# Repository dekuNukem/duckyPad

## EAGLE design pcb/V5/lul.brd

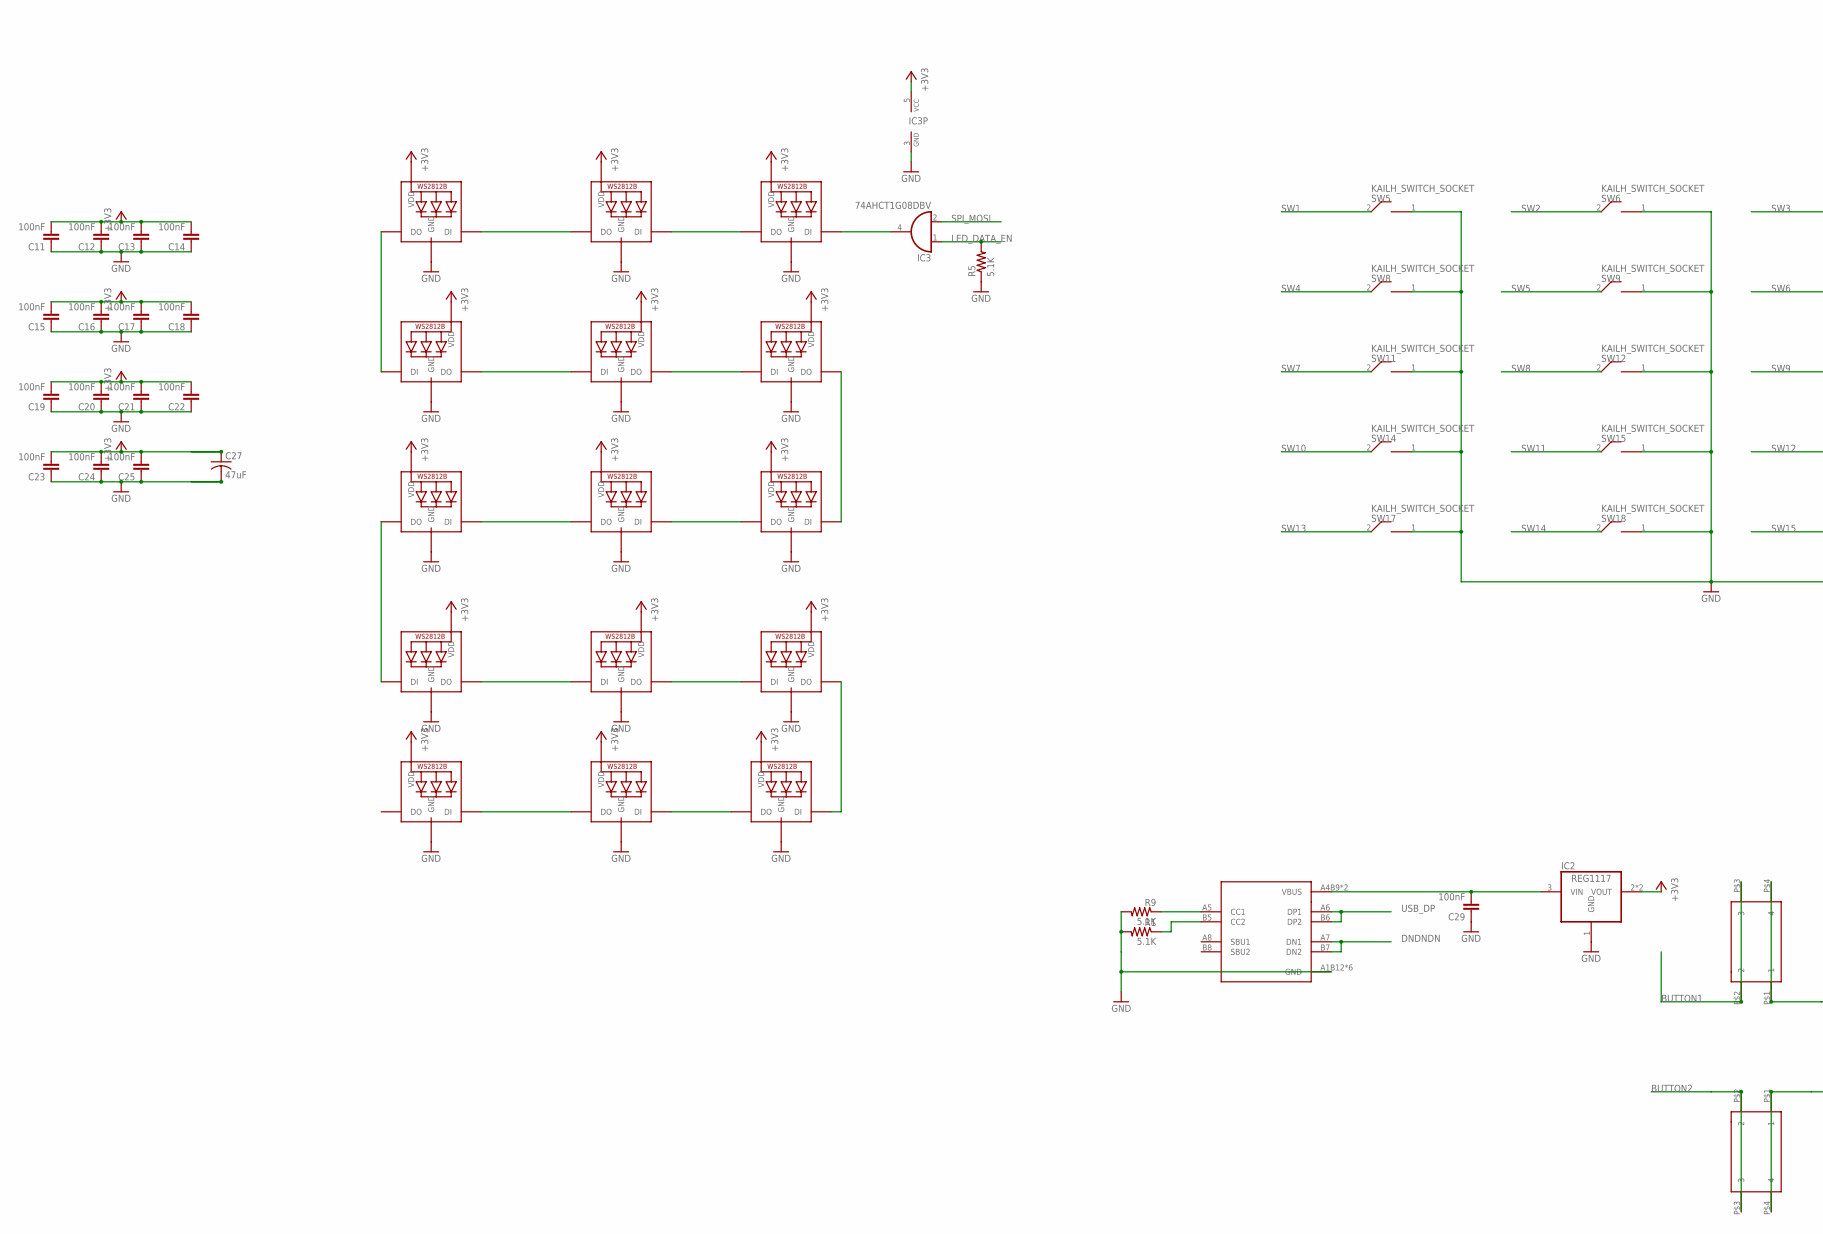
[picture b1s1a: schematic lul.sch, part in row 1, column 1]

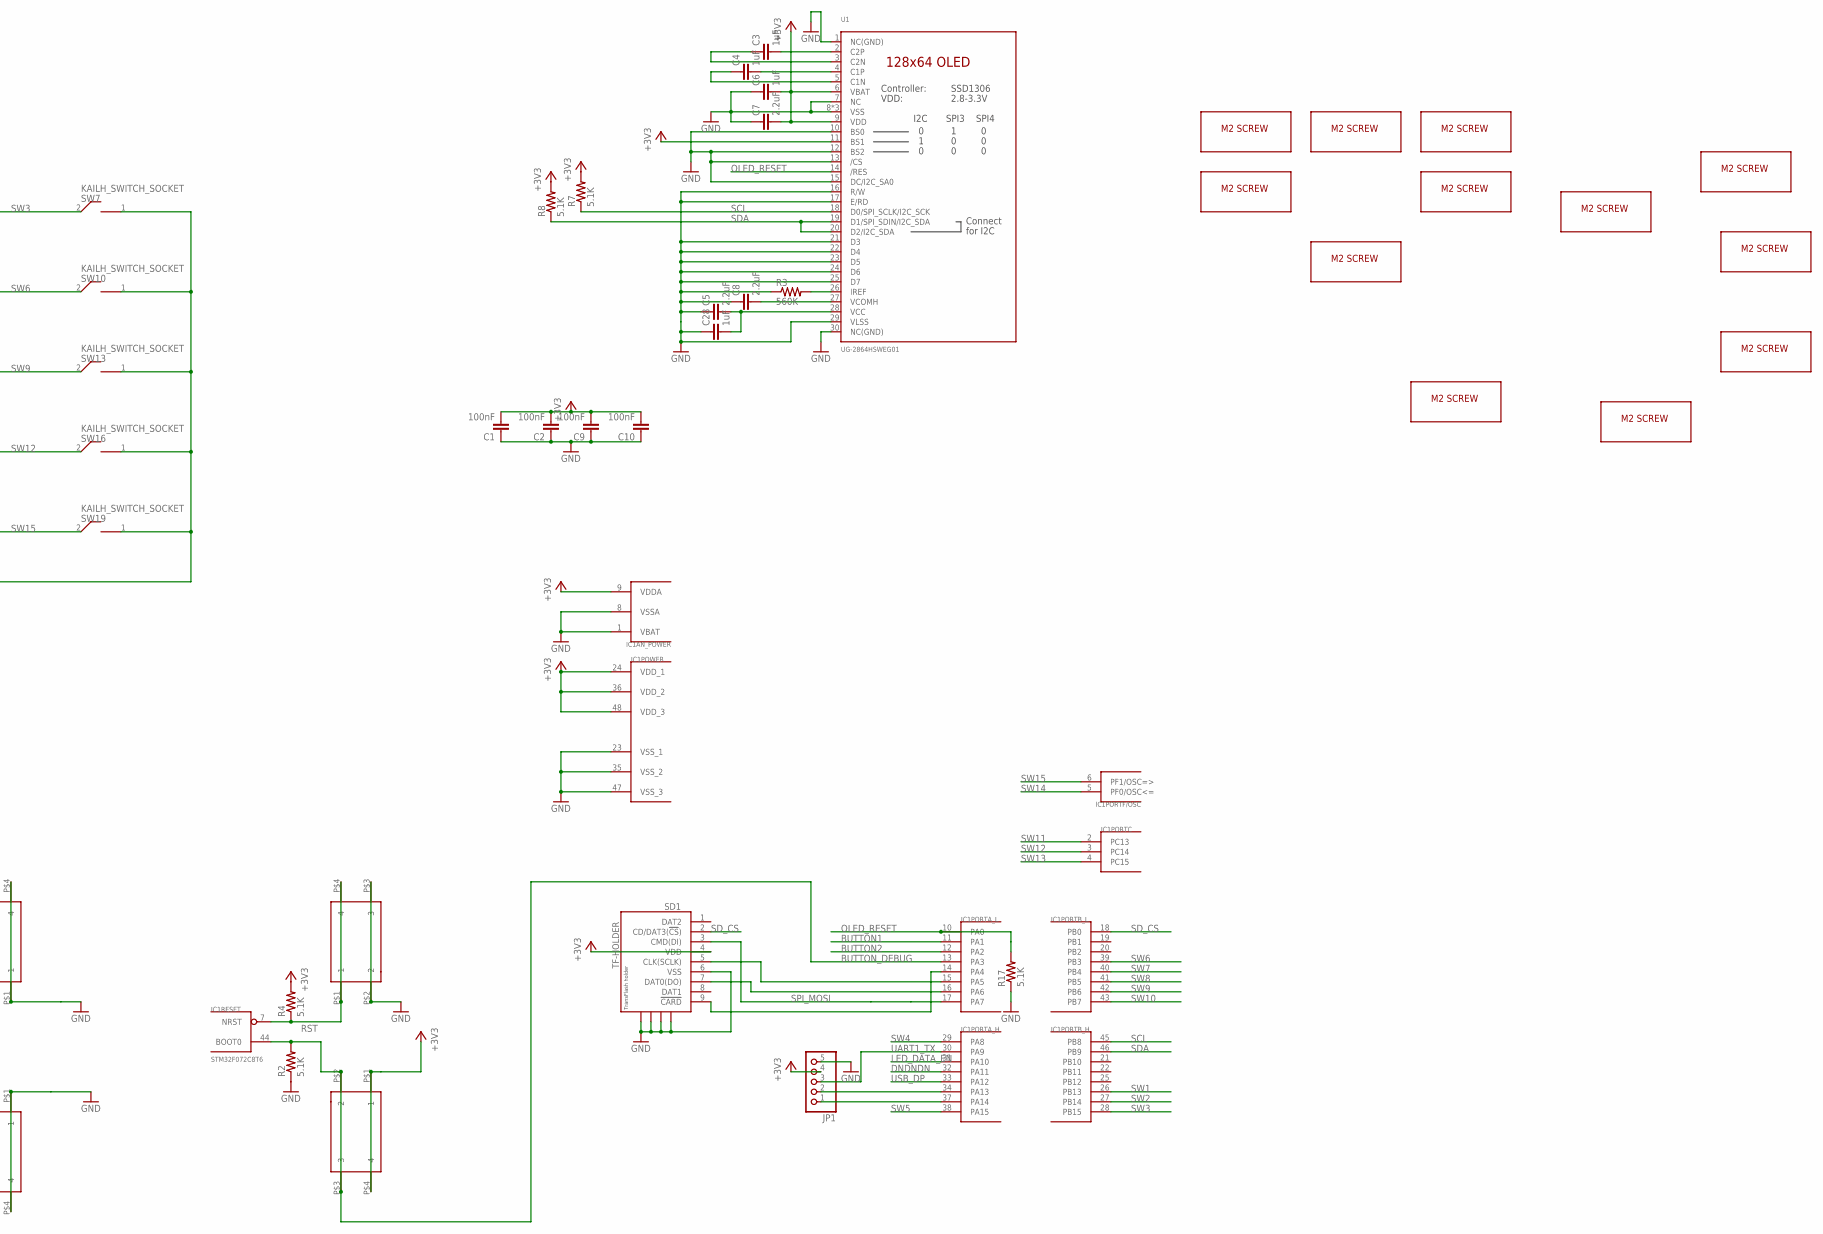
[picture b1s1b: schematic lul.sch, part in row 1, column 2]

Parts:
C1, C2, C9, C10, C11, C12, C13, C14, C15, C16, C17, C18, C19, C20, C21, C22, C23, C24, C25, C29: 100nF; 0805@1
C3, C4, C6, C28: 1uF; 0805@1
C5, C7, C8: 2.2uF; 0805@1
C27: 47uF; C1210
IC1: STM32F072C8T6; TQFP48
IC2: REG1117; SOT223
IC3: 74AHCT1G08DBV; SOT23-5
JP1: PINHD-1X5; 1X05
LED1, LED2, LED3, LED4, LED5, LED6, LED7, LED8, LED9, LED10, LED11, LED12, LED13, LED14, LED15: WS2812B; REVERSE_MNT
R1, R2, R4, R5, R7, R8, R9, R17: 5.1K; 0805
R3: 560K; 0805
SD1: TF-HOLDER; TF-PULL
SW1, SW2: 324_SW324_SWITCH_FOOT_HOLE; 342_SWICH_FOOT_HOLE
SW3, SW4: 324_SW; 342_SWICH_FOOT
SW5, SW6, SW7, SW8, SW9, SW10, SW11, SW12, SW13, SW14, SW15, SW16, SW17, SW18, SW19: KAILH_SWITCH_SOCKET; SWITCH_SOCKET
U1: UG-2864HSWEG01; LUL_UG-2864HSWEG01_1.3_WRAPAROUND
U2: USBC_16P; USBC_16P_FOOT
U$7, U$8, U$9, U$10, U$11, U$12, U$13, U$14, U$15, U$16, U$17, U$23: M2_SCREW_DEV; M2_SCREW_FOOT

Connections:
+3V3: C1.2, C2.2, C6.2, C7.2, C9.2, C10.2, C11.2, C12.2, C13.2, C14.2, C15.2, C16.2, C17.2, C18.2, C19.2, C20.2, C21.2, C22.2, C23.2, C24.2, C25.2, C27.1, IC1.9 (VDDA), IC1.24 (VDD_1), IC1.36 (VDD_2), IC1.48 (VDD_3), IC2.2 (VOUT), IC2.4 (VOUT), IC3.5 (VCC), JP1.4, LED1.VDD, LED2.VDD, LED3.VDD, LED4.VDD, LED5.VDD, LED6.VDD, LED7.VDD, LED8.VDD, LED9.VDD, LED10.VDD, LED11.VDD, LED12.VDD, LED13.VDD, LED14.VDD, LED15.VDD, R4.2, R7.2, R8.2, SD1.4 (VDD), SW1.P$1 (1), SW1.P$4 (4), U1.6 (VBAT), U1.9 (VDD), U1.11 (BS1)
BUTTON1: IC1.11 (PA1), SW3.P$2 (2), SW3.P$3 (3)
BUTTON2: IC1.12 (PA2), SW4.P$2 (2), SW4.P$3 (3)
BUTTON_DEBUG: IC1.13 (PA3), IC1.44 (BOOT0), R2.2, SW1.P$2 (2), SW1.P$3 (3)
DNDNDN: IC1.32 (PA11), U2.A7 (DN1), U2.B7 (DN2)
GND: C1.1, C2.1, C5.1, C6.1, C7.1, C8.1, C9.1, C10.1, C11.1, C12.1, C13.1, C14.1, C15.1, C16.1, C17.1, C18.1, C19.1, C20.1, C21.1, C22.1, C23.1, C24.1, C25.1, C27.2, C28.1, C29.1, IC1.1 (VBAT), IC1.8 (VSSA), IC1.23 (VSS_1), IC1.35 (VSS_2), IC1.47 (VSS_3), IC2.1 (GND), IC3.3 (GND), JP1.5, LED1.GND, LED2.GND, LED3.GND, LED4.GND, LED5.GND, LED6.GND, LED7.GND, LED8.GND, LED9.GND, LED10.GND, LED11.GND, LED12.GND, LED13.GND, LED14.GND, LED15.GND, R1.2, R2.1, R3.1, R5.1, R9.2, R17.1, SD1.6 (VSS), SD1.S1, SD1.S2, SD1.S3, SD1.S4, SW2.P$2 (2), SW2.P$3 (3), SW3.P$1 (1), SW3.P$4 (4), SW4.P$1 (1), SW4.P$4 (4), SW5.1 (2), SW6.1 (2), SW7.1 (2), SW8.1 (2), SW9.1 (2), SW10.1 (2), SW11.1 (2), SW12.1 (2), SW13.1 (2), SW14.1 (2), SW15.1 (2), SW16.1 (2), SW17.1 (2), SW18.1 (2), SW19.1 (2), U1.1 (NC(GND)), U1.7 (NC), U1.8 (VSS), U1.10 (BS0), U1.12 (BS2), U1.13 (/CS), U1.15 (DC/I2C_SA0), U1.16 (R/W), U1.17 (E/RD), U1.21 (D3), U1.22 (D4), U1.23 (D5), U1.24 (D6), U1.25 (D7), U1.29 (VLSS), U1.30 (NC(GND)), U1.31 (VSS), U1.32 (VSS), U2.A1B12 (GND), U2.B11A12 (GND), U2.P$13 (GND), U2.P$14 (GND), U2.P$15 (GND), U2.P$16 (GND)
LED_DATA_EN: IC1.31 (PA10), IC3.1 (I0), R5.2
unnamed: C29.2, IC2.3 (VIN), U2.A4B9 (VBUS), U2.B4A9 (VBUS)
unnamed: R3.2, U1.26 (IREF)
unnamed: C3.2, U1.2 (C2P)
unnamed: C3.1, U1.3 (C2N)
unnamed: C4.2, U1.4 (C1P)
unnamed: C4.1, U1.5 (C1N)
unnamed: IC1.15 (PA5), SD1.5 (CLK(SCLK))
unnamed: LED2.DIN (DI), LED3.DOUT (DO)
unnamed: IC1.16 (PA6), SD1.7 (DAT0(DO))
unnamed: C5.2, C28.2, U1.28 (VCC)
unnamed: C8.2, U1.27 (VCOMH)
unnamed: IC1.14 (PA4), SD1.9 (!CARD)
unnamed: LED1.DIN (DI), LED2.DOUT (DO)
unnamed: LED1.DOUT (DO), LED4.DIN (DI)
unnamed: LED4.DOUT (DO), LED5.DIN (DI)
unnamed: LED5.DOUT (DO), LED6.DIN (DI)
unnamed: LED6.DOUT (DO), LED9.DIN (DI)
unnamed: LED8.DIN (DI), LED9.DOUT (DO)
unnamed: LED7.DIN (DI), LED8.DOUT (DO)
unnamed: LED7.DOUT (DO), LED10.DIN (DI)
unnamed: LED10.DOUT (DO), LED11.DIN (DI)
unnamed: LED11.DOUT (DO), LED12.DIN (DI)
unnamed: LED12.DOUT (DO), LED15.DIN (DI)
unnamed: LED14.DIN (DI), LED15.DOUT (DO)
unnamed: LED13.DIN (DI), LED14.DOUT (DO)
unnamed: IC3.4 (O), LED3.DIN (DI)
unnamed: R1.1, U2.B5 (CC2)
unnamed: IC1.37 (PA14), JP1.1
unnamed: R9.1, U2.A5 (CC1)
unnamed: IC1.34 (PA13), JP1.2
OLED_RESET: IC1.10 (PA0), R17.2, U1.14 (/RES)
RST: IC1.7 (NRST), R4.1, SW2.P$1 (1), SW2.P$4 (4)
SCL: IC1.45 (PB8), R7.1, U1.18 (D0/SPI_SCLK/I2C_SCK)
SDA: IC1.46 (PB9), R8.1, U1.19 (D1/SPI_SDIN/I2C_SDA), U1.20 (D2/I2C_SDA)
SD_CS: IC1.18 (PB0), SD1.2 (CD/DAT3(!CS!))
SPI_MOSI: IC1.17 (PA7), IC3.2 (I1), SD1.3 (CMD(DI))
SW1: IC1.26 (PB13), SW5.2 (1)
SW2: IC1.27 (PB14), SW6.2 (1)
SW3: IC1.28 (PB15), SW7.2 (1)
SW4: IC1.29 (PA8), SW8.2 (1)
SW5: IC1.38 (PA15), SW9.2 (1)
SW6: IC1.39 (PB3), SW10.2 (1)
SW7: IC1.40 (PB4), SW11.2 (1)
SW8: IC1.41 (PB5), SW12.2 (1)
SW9: IC1.42 (PB6), SW13.2 (1)
SW10: IC1.43 (PB7), SW14.2 (1)
SW11: IC1.2 (PC13), SW15.2 (1)
SW12: IC1.3 (PC14), SW16.2 (1)
SW13: IC1.4 (PC15), SW17.2 (1)
SW14: IC1.5 (PF0/OSC<=), SW18.2 (1)
SW15: IC1.6 (PF1/OSC=>), SW19.2 (1)
UART1_TX: IC1.30 (PA9), JP1.3
USB_DP: IC1.33 (PA12), U2.A6 (DP1), U2.B6 (DP2)

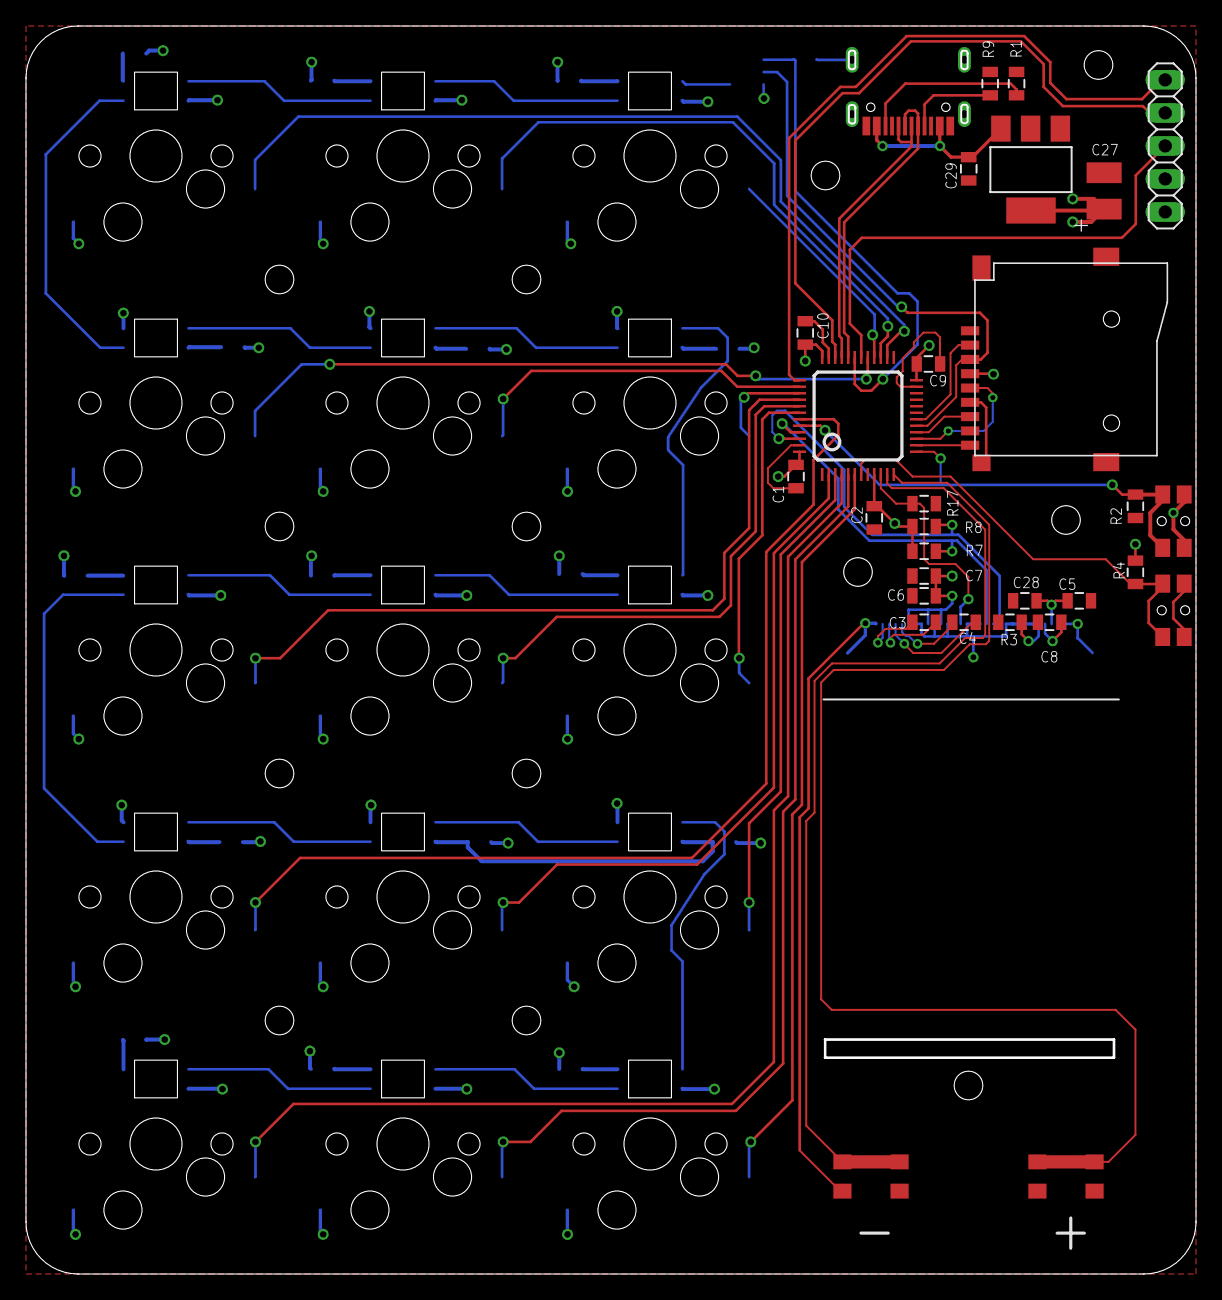
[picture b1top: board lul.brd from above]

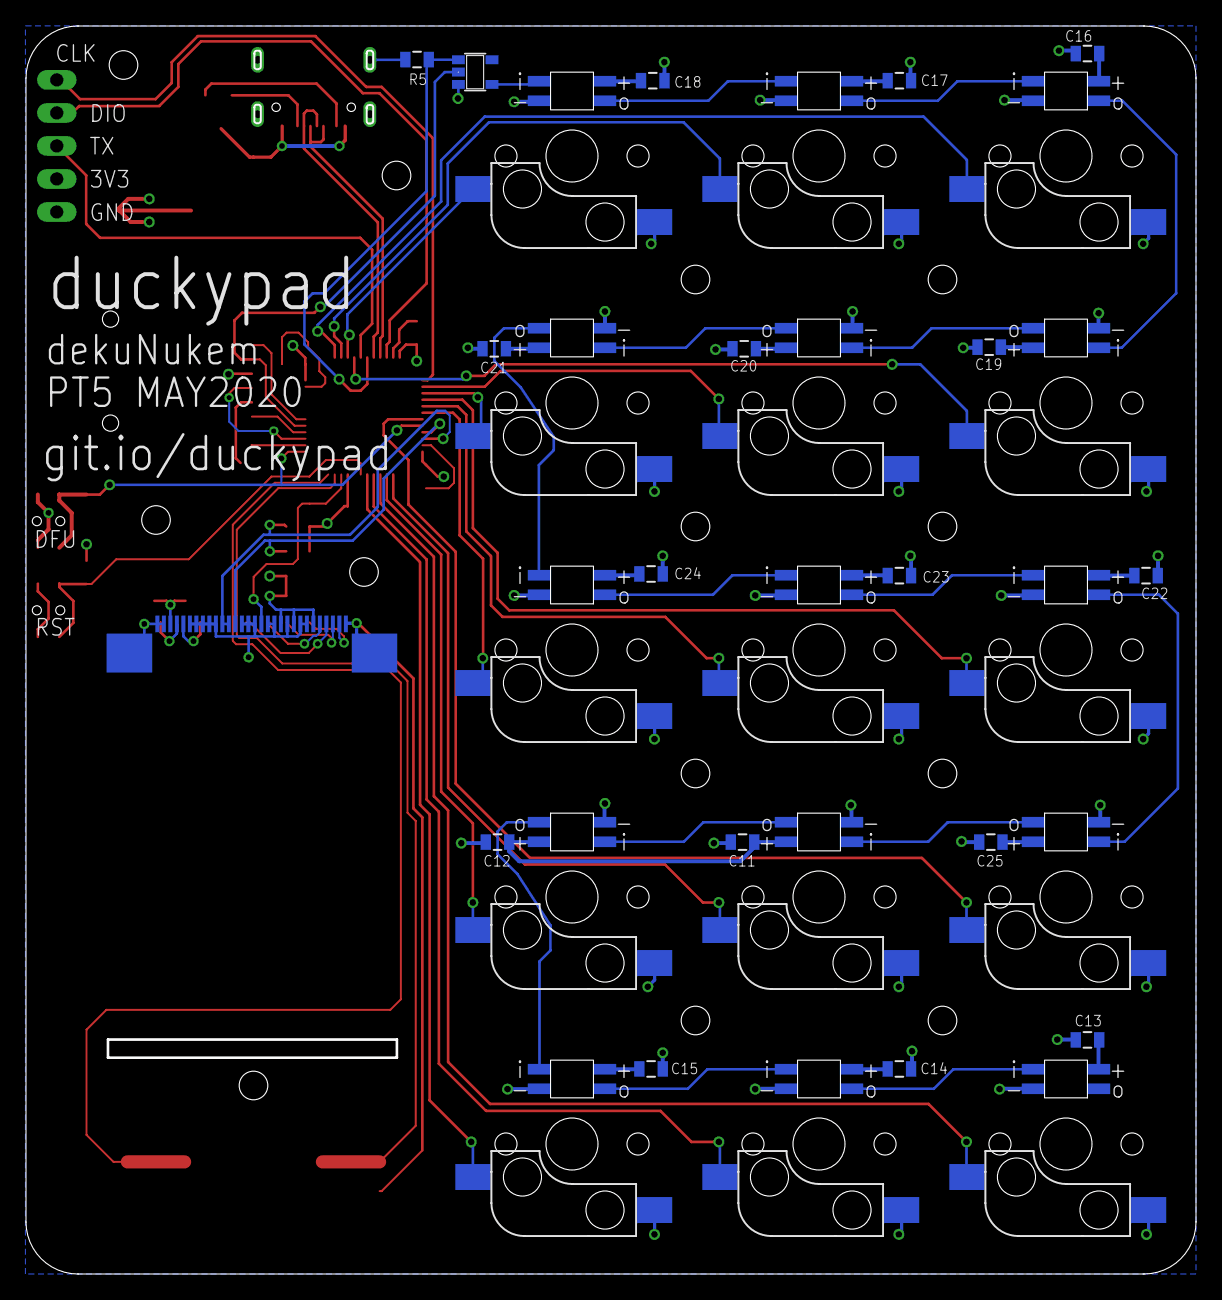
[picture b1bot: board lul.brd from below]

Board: 2 copper layers, 90.0 x 96.0 mm, 91 parts (17 on the bottom side), 60 nets.

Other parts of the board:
U$22: M2_SCREW_DEV; M2_SCREW_FOOT

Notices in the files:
parts and their libraries:
SparkFun-Switches: Licensing: Creative Commons ShareAlike 4.0 International - https://creativecommons.org/licenses/by-sa/4.0
